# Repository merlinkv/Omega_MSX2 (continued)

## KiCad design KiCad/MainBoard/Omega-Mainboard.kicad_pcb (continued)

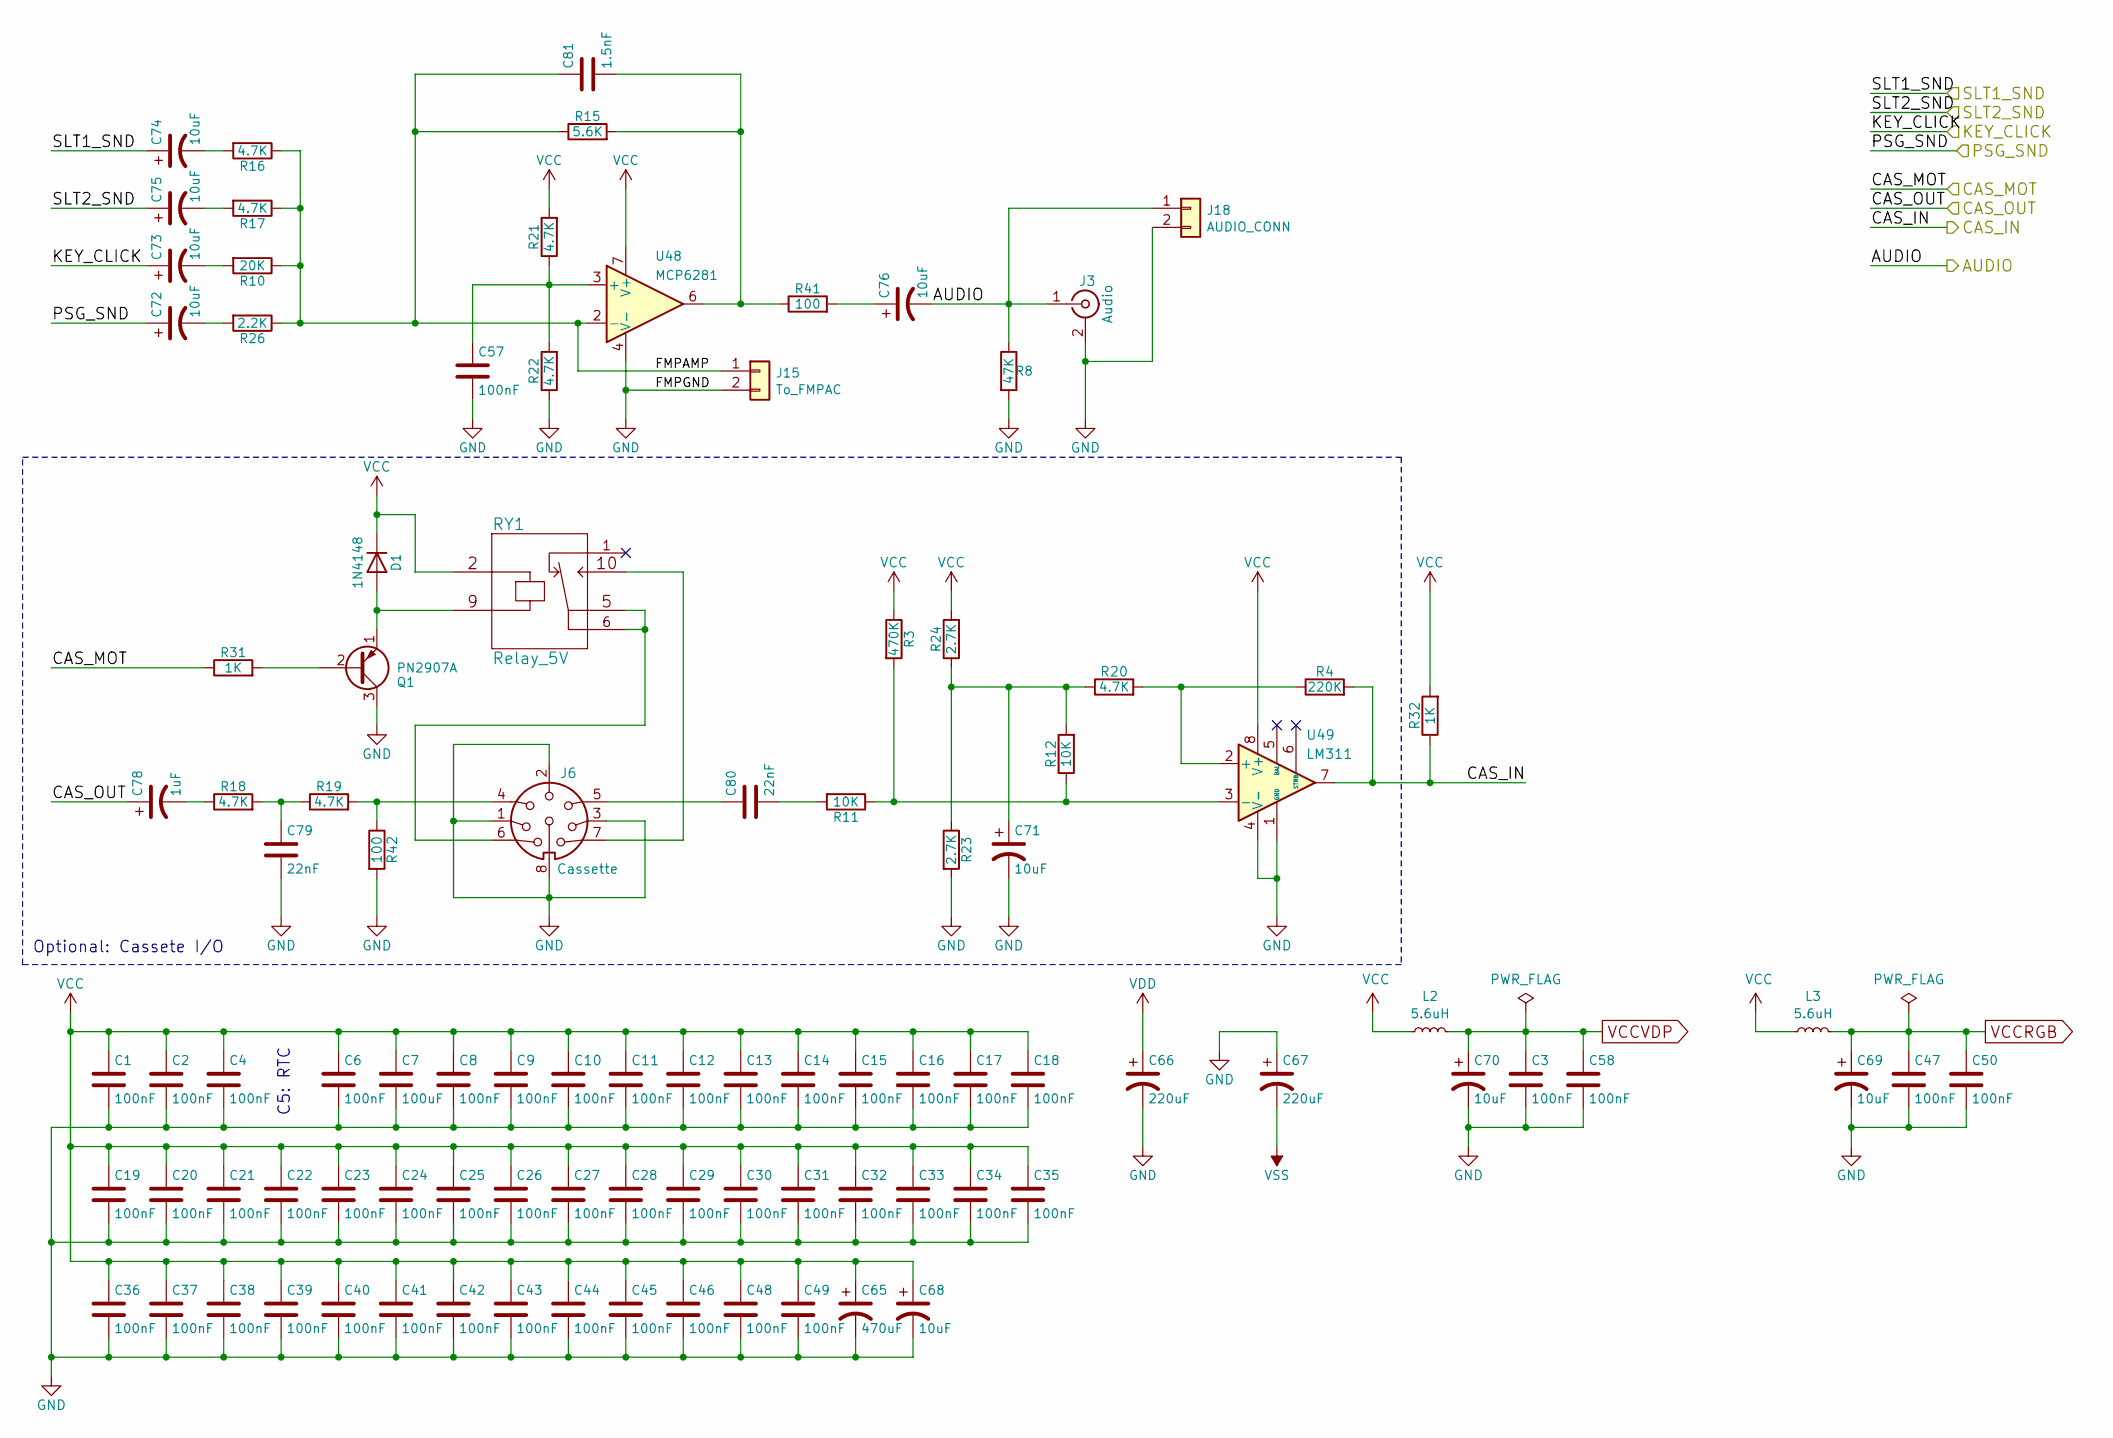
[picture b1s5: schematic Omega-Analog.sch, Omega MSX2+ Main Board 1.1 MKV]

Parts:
C1, C2, C3, C4, C6, C8, C9, C10, C11, C12, C13, C14, C15, C16, C17, C18, C19, C20, C21, C22, C23, C24, C25, C26, C27, C28, C29, C30, C31, C32, C33, C34, C35, C36, C37, C38, C39, C40, C41, C42, C43, C44, C45, C46, C47, C48, C49, C50, C57, C58: 100nF; C_1206_3216Metric_Pad1.42x1.75mm_HandSolder
C7: 100uF; C_1206_3216Metric_Pad1.42x1.75mm_HandSolder
C65: 470uF; CP_Radial_D10.0mm_P5.00mm
C66, C67: 220uF; CP_Radial_D10.0mm_P5.00mm
C68, C69, C70, C71, C72, C73, C74, C75, C76: 10uF; CP_Radial_D5.0mm_P2.50mm
C78: 1uF; CP_Radial_D5.0mm_P2.50mm
C79, C80: 22nF; C_1206_3216Metric_Pad1.42x1.75mm_HandSolder
C81: 1.5nF; C_1206_3216Metric_Pad1.42x1.75mm_HandSolder
D1: 1N4148; D_1206_3216Metric_Pad1.42x1.75mm_HandSolder
J3: Audio; Conn_RCA_Right
J6: Cassette; DIN8
J15: To_FMPAC; Molex_KK-254_AE-6410-02A_1x02_P2.54mm_Vertical
J18: AUDIO_CONN; Molex_KK-254_AE-6410-02A_1x02_P2.54mm_Vertical
L2, L3: 5.6uH; L_1206_3216Metric_Pad1.42x1.75mm_HandSolder
Q1: PN2907A; TO-92L_Inline_Wide
R3: 470K; R_1206_3216Metric_Pad1.42x1.75mm_HandSolder
R4: 220K; R_1206_3216Metric_Pad1.42x1.75mm_HandSolder
R8: 47K; R_1206_3216Metric_Pad1.42x1.75mm_HandSolder
R10: 20K; R_1206_3216Metric_Pad1.42x1.75mm_HandSolder
R11, R12: 10K; R_1206_3216Metric_Pad1.42x1.75mm_HandSolder
R15: 5.6K; R_1206_3216Metric_Pad1.42x1.75mm_HandSolder
R16, R17, R18, R19, R20, R21, R22: 4.7K; R_1206_3216Metric_Pad1.42x1.75mm_HandSolder
R23, R24: 2.7K; R_1206_3216Metric_Pad1.42x1.75mm_HandSolder
R26: 2.2K; R_1206_3216Metric_Pad1.42x1.75mm_HandSolder
R31, R32: 1K; R_1206_3216Metric_Pad1.42x1.75mm_HandSolder
R41, R42: 100; R_1206_3216Metric_Pad1.42x1.75mm_HandSolder
RY1: Relay_5V; Relay_SPDT
U48: MCP6281; DIP-8_W7.62mm_Socket
U49: LM311; DIP-8_W7.62mm_Socket

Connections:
/AUDIO: C76.2, J3.1 (In), J18.1, R8.1; also elsewhere on the board
/Analog/FMPAMP: C81.1, J15.1, R10.1, R15.1, R16.1, R17.1, R26.1, U48.2 (-)
/CAS_IN: R4.2, R32.1, U49.7; also elsewhere on the board
/CAS_MOT: R31.1; also elsewhere on the board
/CAS_OUT: C78.1; also elsewhere on the board
/KEY_CLICK: C73.1; also elsewhere on the board
/PSG_SND: C72.1; also elsewhere on the board
/SLT1_SND: C74.1; also elsewhere on the board
/SLT2_SND: C75.1; also elsewhere on the board
GND: C1.2, C2.2, C3.2, C4.2, C6.2, C7.2, C8.2, C9.2, C10.2, C11.2, C12.2, C13.2, C14.2, C15.2, C16.2, C17.2, C18.2, C19.2, C20.2, C21.2, C22.2, C23.2, C24.2, C25.2, C26.2, C27.2, C28.2, C29.2, C30.2, C31.2, C32.2, C33.2, C34.2, C35.2, C36.2, C37.2, C38.2, C39.2, C40.2, C41.2, C42.2, C43.2, C44.2, C45.2, C46.2, C47.2, C48.2, C49.2, C50.2, C57.2, C58.2, C65.2, C66.2, C67.1, C68.2, C69.2, C70.2, C71.2, C79.2, J3.2 (Ext), J6.1, J6.2, J6.3, J6.8, J15.2, J18.2, Q1.3 (C), R8.2, R22.1, R23.2, R42.2, U48.4 (V-), U49.1 (GND), U49.4 (V-); also elsewhere on the board
unnamed: C57.1, R21.1, R22.2, U48.3 (+)
unnamed: C71.1, R12.2, R20.1, R23.1, R24.1
unnamed: C72.2, R26.2
unnamed: C73.2, R10.2
unnamed: C74.2, R16.2
unnamed: C75.2, R17.2
unnamed: C76.1, R41.2
unnamed: C78.2, R18.1
unnamed: C79.1, R18.2, R19.1
unnamed: C80.1, J6.5
unnamed: C80.2, R11.2
unnamed: C81.2, R15.2, R41.1, U48.6
unnamed: D1.2 (A), Q1.1 (E), RY1.9
unnamed: J6.4, R19.2, R42.1
unnamed: J6.6, RY1.5, RY1.6
unnamed: J6.7, RY1.10
unnamed: Q1.2 (B), R31.2
unnamed: R3.2, R11.1, R12.1, U49.3 (-)
unnamed: R4.1, R20.2, U49.2 (+)
VCC: C1.1, C2.1, C4.1, C6.1, C7.1, C8.1, C9.1, C10.1, C11.1, C12.1, C13.1, C14.1, C15.1, C16.1, C17.1, C18.1, C19.1, C20.1, C21.1, C22.1, C23.1, C24.1, C25.1, C26.1, C27.1, C28.1, C29.1, C30.1, C31.1, C32.1, C33.1, C34.1, C35.1, C36.1, C37.1, C38.1, C39.1, C40.1, C41.1, C42.1, C43.1, C44.1, C45.1, C46.1, C48.1, C49.1, C65.1, C68.1, D1.1 (K), L2.1, L3.1, R3.1, R21.2, R24.2, R32.2, RY1.2, U48.7 (V+), U49.8 (V+); also elsewhere on the board
VCCRGB: C47.1, C50.1, C69.1, L3.2; also elsewhere on the board
VCCVDP: C3.1, C58.1, C70.1, L2.2; also elsewhere on the board
VDD: C66.1; also elsewhere on the board
VSS: C67.2; also elsewhere on the board

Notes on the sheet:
C5: RTC
Optional: Cassete I/O

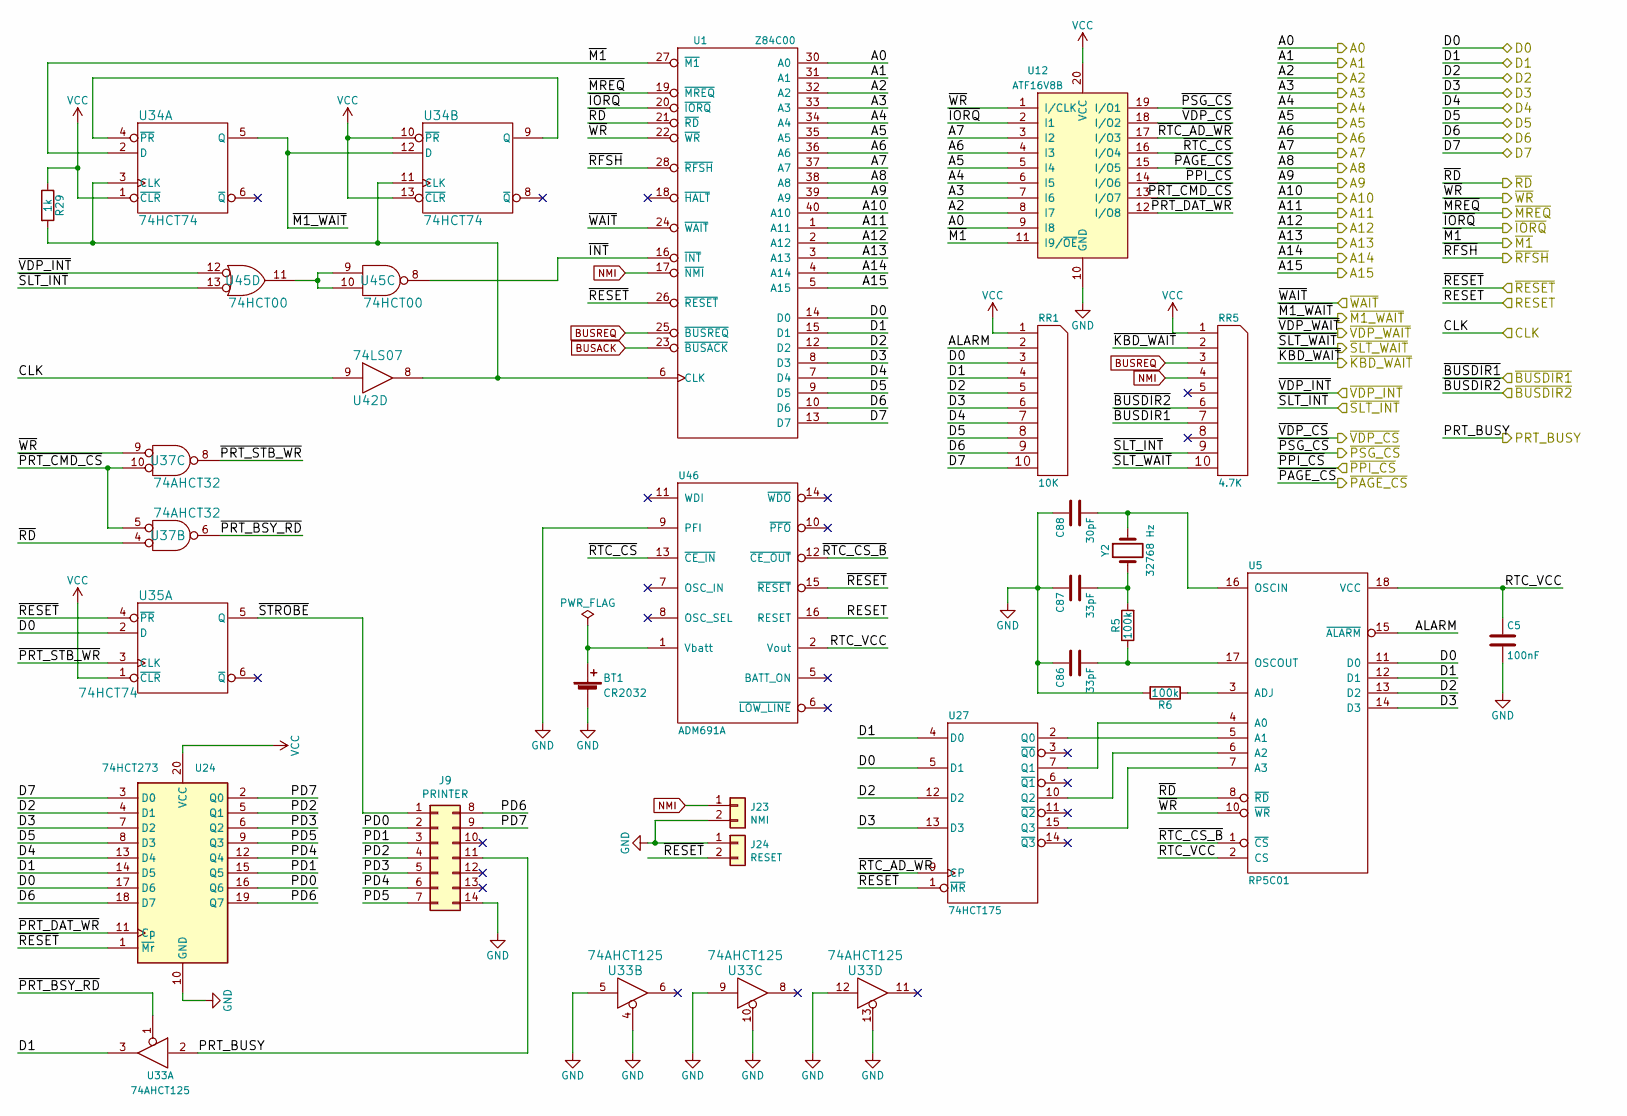
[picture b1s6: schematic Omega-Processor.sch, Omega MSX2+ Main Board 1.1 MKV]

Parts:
BT1: CR2032; Battery_Holder_CR2032_Universal
C5: 100nF; C_1206_3216Metric_Pad1.42x1.75mm_HandSolder
C86, C87: 33pF; C_1206_3216Metric_Pad1.42x1.75mm_HandSolder
C88: 30pF; C_1206_3216Metric_Pad1.42x1.75mm_HandSolder
J9: PRINTER; Conn_Micro_Ribbon_14F
J23: NMI; Molex_KK-254_AE-6410-02A_1x02_P2.54mm_Vertical
J24: RESET; Molex_KK-254_AE-6410-02A_1x02_P2.54mm_Vertical
R5, R6: 100k; R_1206_3216Metric_Pad1.42x1.75mm_HandSolder
R29: 1k; R_1206_3216Metric_Pad1.42x1.75mm_HandSolder
RR1: 10K; R_Array_SIP10
RR5: 4.7K; R_Array_SIP10
U1: Z84C00; DIP-40_W15.24mm_Socket
U5: RP5C01; DIP-18_W7.62mm_Socket
U12: ATF16V8B; DIP-20_W7.62mm_Socket
U24: 74HCT273; DIP-20_W7.62mm_Socket
U27: 74HCT175; DIP-16_W7.62mm_Socket
U33: 74AHCT125; DIP-14_W7.62mm_Socket
U34, U35: 74HCT74; DIP-14_W7.62mm_Socket
U37: 74AHCT32; IC_DIP14_300
U42: 74LS07; IC_DIP14_300
U45: 74HCT00; IC_DIP14_300
U46: ADM691A; DIP-16_W7.62mm_Socket
Y2: 32768 Hz; Crystal_C38-LF_D3.0mm_L8.0mm_Horizontal_1EP_style2

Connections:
/A0: U1.30 (A0), U12.9 (I8); also elsewhere on the board
/A1: U1.31 (A1); also elsewhere on the board
/A2: U1.32 (A2), U12.8 (I7); also elsewhere on the board
/A3: U1.33 (A3), U12.7 (I6); also elsewhere on the board
/A4: U1.34 (A4), U12.6 (I5); also elsewhere on the board
/A5: U1.35 (A5), U12.5 (I4); also elsewhere on the board
/A6: U1.36 (A6), U12.4 (I3); also elsewhere on the board
/A7: U1.37 (A7), U12.3 (I2); also elsewhere on the board
/A8: U1.38 (A8); also elsewhere on the board
/A9: U1.39 (A9); also elsewhere on the board
/A10: U1.40 (A10); also elsewhere on the board
/A11: U1.1 (A11); also elsewhere on the board
/A12: U1.2 (A12); also elsewhere on the board
/A13: U1.3 (A13); also elsewhere on the board
/A14: U1.4 (A14); also elsewhere on the board
/A15: U1.5 (A15); also elsewhere on the board
/CLK: U42.9; also elsewhere on the board
/D0: RR1.3, U1.14 (D0), U5.11 (D0), U24.17 (D6), U27.5 (D1), U35.2 (D); also elsewhere on the board
/D1: RR1.4, U1.15 (D1), U5.12 (D1), U24.14 (D5), U27.4 (D0), U33.3; also elsewhere on the board
/D2: RR1.5, U1.12 (D2), U5.13 (D2), U24.4 (D1), U27.12 (D2); also elsewhere on the board
/D3: RR1.6, U1.8 (D3), U5.14 (D3), U24.7 (D2), U27.13 (D3); also elsewhere on the board
/D4: RR1.7, U1.7 (D4), U24.13 (D4); also elsewhere on the board
/D5: RR1.8, U1.9 (D5), U24.8 (D3); also elsewhere on the board
/D6: RR1.9, U1.10 (D6), U24.18 (D7); also elsewhere on the board
/D7: RR1.10, U1.13 (D7), U24.3 (D0); also elsewhere on the board
/Memory/~PAGE_RD: U37.3; also elsewhere on the board
/Memory/~PAGE_WR: U37.11; also elsewhere on the board
/PRT_BUSY: J9.11, U33.2; also elsewhere on the board
/Processor/ALARM: RR1.2, U5.15 (~ALARM)
/Processor/PD0: J9.2, U24.16 (Q6)
/Processor/PD1: J9.3, U24.15 (Q5)
/Processor/PD2: J9.4, U24.5 (Q1)
/Processor/PD3: J9.5, U24.6 (Q2)
/Processor/PD4: J9.6, U24.12 (Q4)
/Processor/PD5: J9.7, U24.9 (Q3)
/Processor/PD6: J9.8, U24.19 (Q7)
/Processor/PD7: J9.9, U24.2 (Q0)
/Processor/RTC_VCC: C5.1, U5.2 (CS), U5.18 (VCC), U46.2 (Vout)
/Processor/~INT: U1.16 (~INT), U45.8
/Processor/~PRT_BSY_RD: U33.1, U37.6
/Processor/~PRT_CMD_CS: U12.13 (I/O7), U37.5, U37.10
/Processor/~PRT_DAT_WR: U12.12 (I/O8), U24.11 (Cp)
/Processor/~PRT_STB_WR: U35.3 (CLK), U37.8
/Processor/~RTC_AD_WR: U12.17 (I/O3), U27.9 (CP)
/Processor/~RTC_CS: U12.16 (I/O4), U46.13 (~CE_IN)
/Processor/~RTC_CS_B: U5.1 (~CS), U46.12 (~CE_OUT)
/Processor/~STROBE: J9.1, U35.5 (Q)
/RESET: U46.16 (RESET); also elsewhere on the board
/~BUSDIR1: RR5.7; also elsewhere on the board
/~BUSDIR2: RR5.6; also elsewhere on the board
/~IORQ: U1.20 (~IORQ), U12.2 (I1); also elsewhere on the board
/~KBD_WAIT: RR5.2; also elsewhere on the board
/~M1: U1.27 (~M1), U12.11 (I9/~OE), U34.2 (D); also elsewhere on the board
/~M1_WAIT: U34.5 (Q), U34.12 (D); also elsewhere on the board
/~MREQ: U1.19 (~MREQ); also elsewhere on the board
/~PAGE_CS: U12.15 (I/O5), U37.2, U37.12
/~PPI_CS: U12.14 (I/O6), U45.4; also elsewhere on the board
/~PSG_CS: U12.19 (I/O1); also elsewhere on the board
/~RD: U1.21 (~RD), U5.8 (~RD), U37.1, U37.4; also elsewhere on the board
/~RESET: J24.2, U1.26 (~RESET), U24.1 (~Mr), U27.1 (~MR), U35.4 (~PR), U45.2, U46.15 (~RESET); also elsewhere on the board
/~RFSH: U1.28 (~RFSH); also elsewhere on the board
/~SLT_INT: RR5.9, U45.13; also elsewhere on the board
/~SLT_WAIT: RR5.10; also elsewhere on the board
/~VDP_CS: U12.18 (I/O2); also elsewhere on the board
/~VDP_INT: U45.12; also elsewhere on the board
/~WAIT: U1.24 (~WAIT); also elsewhere on the board
/~WR: U1.22 (~WR), U5.10 (~WR), U12.1 (I/CLK), U37.9, U37.13; also elsewhere on the board
BUSACK: U1.23 (~BUSACK); also elsewhere on the board
BUSREQ: RR5.3, U1.25 (~BUSREQ); also elsewhere on the board
GND: BT1.2 (-), C5.2, C86.1, C87.1, C88.1, J9.14, J23.2, J24.1, R6.2, U1.29 (GND), U5.9 (GND), U12.10 (GND), U24.10 (GND), U27.8 (GND), U33.4, U33.5, U33.7 (GND), U33.9, U33.10, U33.12, U33.13, U34.7 (GND), U35.7 (GND), U37.7 (GND), U42.7 (GND), U45.7 (GND), U46.4 (GND), U46.9 (PFI); also elsewhere on the board
NMI: J23.1, RR5.4, U1.17 (~NMI); also elsewhere on the board
unnamed: BT1.1 (+), U46.1 (Vbatt)
unnamed: C86.2, R5.1, U5.17 (OSCOUT)
unnamed: C87.2, R5.2, Y2.2
unnamed: C88.2, U5.16 (OSCIN), Y2.1
unnamed: R6.1, U5.3 (ADJ)
unnamed: R29.2, U1.6 (CLK), U34.3 (CLK), U34.11 (CLK), U42.8
unnamed: U5.5 (A1), U27.2 (Q0)
unnamed: U5.4 (A0), U27.7 (Q1)
unnamed: U5.6 (A2), U27.10 (Q2)
unnamed: U5.7 (A3), U27.15 (Q3)
unnamed 379: U45.3, U45.5; also elsewhere on the board
unnamed: U34.4 (~PR), U34.9 (Q)
unnamed: U45.1, U45.6
unnamed: U45.9, U45.10, U45.11
VCC: R29.1, RR1.1 (COM), RR5.1 (COM), U1.11 (VCC), U12.20 (VCC), U24.20 (VCC), U27.16 (VCC), U33.14 (VCC), U34.1 (~CLR), U34.10 (~PR), U34.13 (~CLR), U34.14 (VCC), U35.1 (~CLR), U35.14 (VCC), U37.14 (VCC), U42.14 (VCC), U45.14 (VCC), U46.3 (VCC); also elsewhere on the board

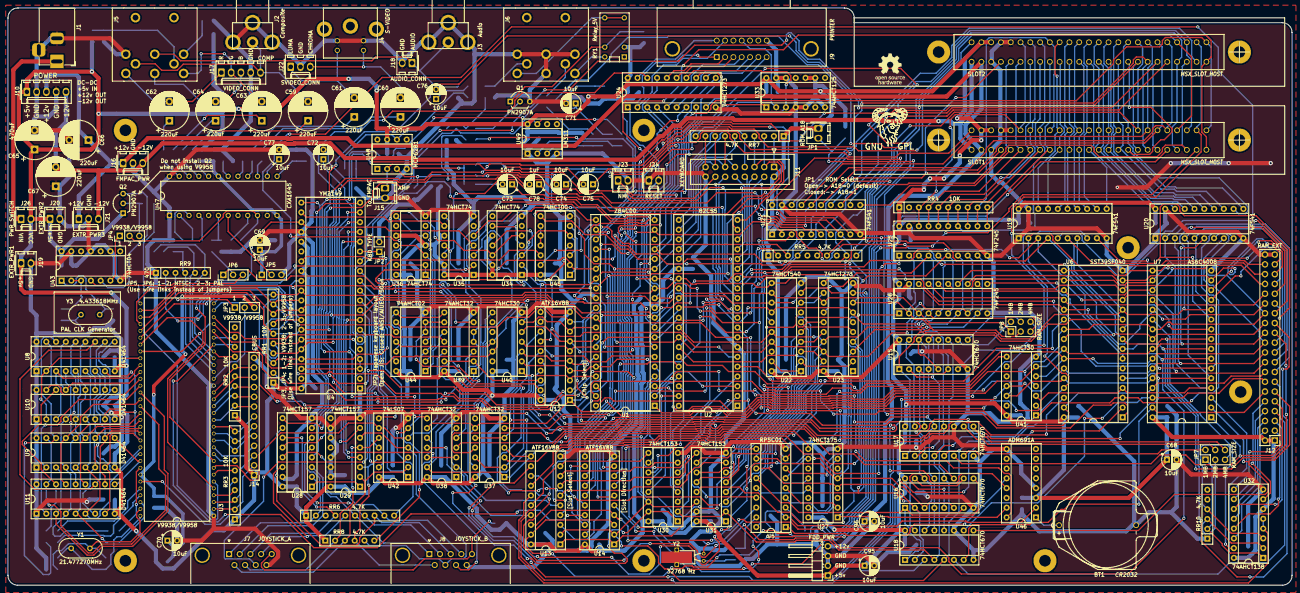
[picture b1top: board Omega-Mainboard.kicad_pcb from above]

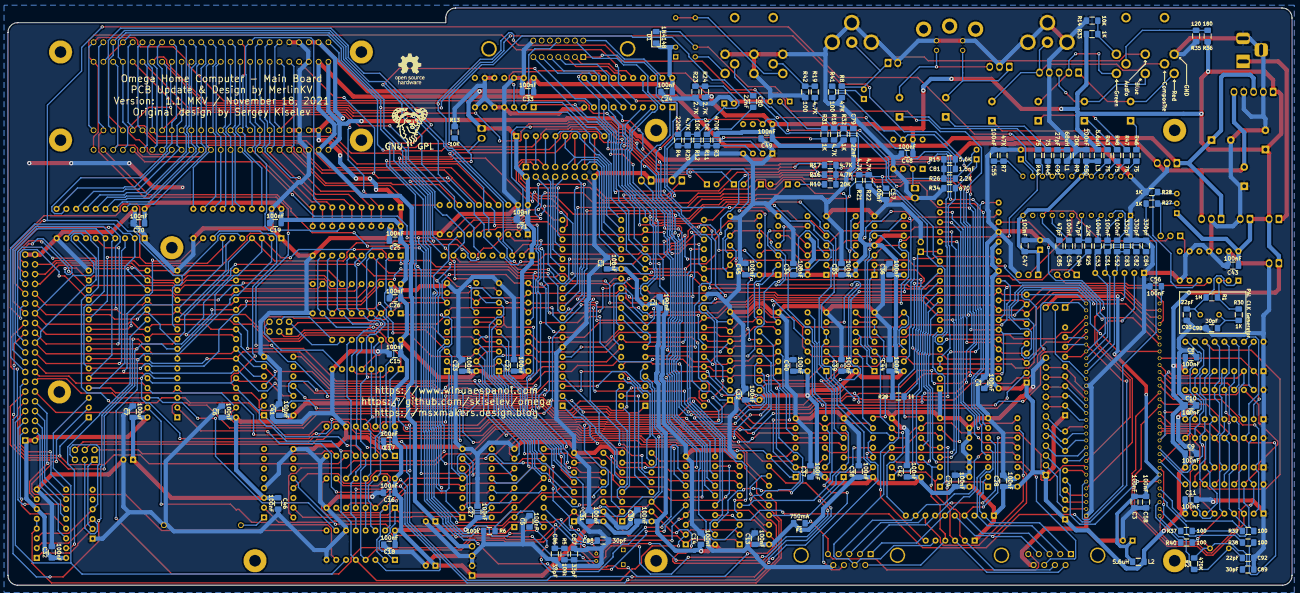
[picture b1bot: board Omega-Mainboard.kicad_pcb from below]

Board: 2 copper layers, 333.4 x 149.9 mm, 261 parts (127 on the bottom side), 365 nets.

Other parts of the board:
J11: KEYBOARD; IDC-Header_2x08_P2.54mm_Vertical
J12: RAM_EXT; PinHeader_2x20_P2.54mm_Vertical
JP1: ROM_A18; Molex_KK-254_AE-6410-02A_1x02_P2.54mm_Vertical
JP7, JP8: RAM_SIZE; PinHeader_2x03_P2.54mm_Vertical
R13: 10K; R_1206_3216Metric_Pad1.42x1.75mm_HandSolder
RR7: 4.7K; R_Array_SIP10
RR10: 4.7K; R_Array_SIP6
U2: 82C55; DIP-40_W15.24mm_Socket
U6: SST39SF040; DIP-32_W15.24mm_Socket
U7: AS6C4008; DIP-32_W15.24mm_Socket
U13: ATF16V8B; DIP-20_W7.62mm_Socket
U15, U16, U17, U18: 74HCT670; DIP-16_W7.62mm_Socket
U22: 74HCT540; DIP-20_W7.62mm_Socket
U23: 74HCT273; DIP-20_W7.62mm_Socket
U26: 74F245; DIP-20_W7.62mm_Socket
U30, U31: 74HCT153; DIP-16_W7.62mm_Socket
U32: 74AHCT138; DIP-16_W7.62mm_Socket
U38: 74AHCT32; DIP-14_W7.62mm_Socket
U40, U41: 74HCT30; DIP-14_W7.62mm_Socket

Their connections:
/A0: J12.31, U2.9, U6.12, U7.12, U15.5, U15.14, U16.5, U16.14, U17.14, U18.14, U40.12; also elsewhere on the board
/A1: J12.29, U2.8, U6.11, U7.11, U15.4, U15.13, U16.4, U16.13, U17.13, U18.13, U40.11; also elsewhere on the board
/A2: J12.27, U6.10, U7.10, U40.6; also elsewhere on the board
/A3: J12.25, U6.9, U7.9, U40.5; also elsewhere on the board
/A4: J12.23, U6.8, U7.8, U40.4; also elsewhere on the board
/A5: J12.21, U6.7, U7.7, U40.3; also elsewhere on the board
/A6: J12.19, U6.6, U7.6, U40.2; also elsewhere on the board
/A7: J12.17, U6.5, U7.5, U40.1; also elsewhere on the board
/A8: J12.20, U6.27, U7.27, U41.11; also elsewhere on the board
/A9: J12.22, U6.26, U7.26, U41.5; also elsewhere on the board
/A10: J12.28, U6.23, U7.23, U41.4; also elsewhere on the board
/A11: J12.24, U6.25, U7.25, U41.6; also elsewhere on the board
/A12: J12.15, U6.4, U7.4, U41.3; also elsewhere on the board
/A13: J12.18, U6.28, U7.28, U41.12; also elsewhere on the board
/A14: U6.29, U13.2, U17.5, U18.5, U30.14, U31.14, U41.2; also elsewhere on the board
/A15: U6.3, U13.1, U17.4, U18.4, U30.2, U31.2, U41.1; also elsewhere on the board
/CAS_MOT: U2.13; also elsewhere on the board
/CAS_OUT: U2.12; also elsewhere on the board
/D0: U2.34, U16.3, U16.6, U18.3, U22.18, U23.3, U26.9; also elsewhere on the board
/D1: U2.33, U16.2, U16.7, U18.2, U22.17, U23.18, U26.8; also elsewhere on the board
/D2: U2.32, U16.1, U16.9, U18.1, U22.16, U23.17, U26.7; also elsewhere on the board
/D3: U2.31, U16.10, U16.15, U18.15, U22.15, U23.4, U26.6; also elsewhere on the board
/D4: U2.30, U15.3, U15.6, U17.3, U22.14, U23.7, U26.5; also elsewhere on the board
/D5: JP8.5, U2.29, U15.2, U17.2, U22.13, U23.14, U26.4; also elsewhere on the board
/D6: JP8.1, U2.28, U15.15, U17.15, U22.12, U23.13, U26.3; also elsewhere on the board
/D7: JP8.3, U2.27, U15.1, U17.1, U22.11, U23.8, U26.2; also elsewhere on the board
/KANA_LED: J11.14; also elsewhere on the board
/KEY_CLICK: U2.10; also elsewhere on the board
/Memory/MD0: J12.33, U6.13, U7.13, U26.11
/Memory/MD1: J12.35, U6.14, U7.14, U26.12
/Memory/MD2: J12.37, U6.15, U7.15, U26.13
/Memory/MD3: J12.38, U6.17, U7.17, U26.14
/Memory/MD4: J12.36, U6.18, U7.18, U26.15
/Memory/MD5: J12.34, U6.19, U7.19, U26.16
/Memory/MD6: J12.32, U6.20, U7.20, U26.17
/Memory/MD7: J12.30, U6.21, U7.21, U26.18
/Memory/RAM_A14: J12.13, U7.3, U18.6
/Memory/RAM_A15: J12.12, U7.31, U18.7
/Memory/RAM_A16: J12.11, U7.2, U18.9
/Memory/RAM_A17: J12.14, U7.30, U18.10
/Memory/RAM_A18: J12.9, U7.1, U17.6
/Memory/RAM_A19: JP7.2, U17.7
/Memory/RAM_A20: JP7.4, U17.10
/Memory/RAM_A21: JP7.6, U17.9
/Memory/ROM_A18: JP1.2, R13.1, U6.1
/Memory/~PAGE_RD: U15.11, U16.11; also elsewhere on the board
/Memory/~PAGE_WR: U15.12, U16.12, U17.12, U18.12; also elsewhere on the board
/Memory/~RAM0_CS: U7.22, U32.15
/Memory/~RAM1_CS: J12.4, U32.14
/Memory/~RAM2_CS: J12.3, U32.13
/Memory/~RAM3_CS: J12.6, U32.12
/Memory/~RAM4_CS: J12.5, U32.11
/Memory/~RAM5_CS: J12.8, U32.10
/Memory/~RAM6_CS: J12.7, U32.9
/Memory/~RAM7_CS: J12.10, U32.7
/PPI/CAPS_LED: J11.12, U2.11
/PPI/COLUMN0: J11.1, RR7.2, U2.18
/PPI/COLUMN1: J11.3, RR7.3, U2.19
/PPI/COLUMN2: J11.5, RR7.4, U2.20
/PPI/COLUMN3: J11.7, RR7.5, U2.21
/PPI/COLUMN4: J11.9, RR7.6, U2.22
/PPI/COLUMN5: J11.11, RR7.7, U2.23
/PPI/COLUMN6: J11.13, RR7.8, U2.24
/PPI/COLUMN7: J11.15, RR7.9, U2.25
/PPI/ROW_A: J11.4, U2.14
/PPI/ROW_B: J11.6, U2.15
/PPI/ROW_C: J11.8, U2.16
/PPI/ROW_D: J11.10, U2.17
/PPI/SB_SLT_A: U13.6, U31.7
/PPI/SB_SLT_B: U13.7, U31.9
/PPI/SLT_A: U13.8, U30.7
/PPI/SLT_B: U13.9, U30.9
/PPI/~FFFF: U13.5, U38.2, U38.6
/PPI/~SLTSL3: U13.17, U38.1
/PPI/~SUB_RD: U22.1, U22.19, U38.11
/PPI/~SUB_REG_CS: U38.3, U38.10, U38.12
/PPI/~SUB_WR: U23.11, U38.8
/PRT_BUSY: RR7.10; also elsewhere on the board
/RESET: U2.35; also elsewhere on the board
/ROM_A16: U6.2, U13.13
/ROM_A17: U6.30, U13.12
/~MEM_RD: U13.16, U26.1
/~MREQ: U13.3; also elsewhere on the board
/~PPI_CS: U2.6; also elsewhere on the board
/~RAM_SL: U13.15, U32.4, U32.5
/~RD: J12.26, U2.5, U6.24, U7.24, U13.11, U38.13; also elsewhere on the board
/~RESET: U23.1; also elsewhere on the board
/~RFSH: U13.4; also elsewhere on the board
/~ROM_CS: U6.22, U13.14
/~SLTSL1: U13.19; also elsewhere on the board
/~SLTSL2: U13.18; also elsewhere on the board
/~WR: J12.16, U2.36, U6.31, U7.29, U38.9; also elsewhere on the board
GND: J11.16, J12.39, J12.40, R13.2, RR10.1, U2.7, U6.16, U7.16, U13.10, U15.8, U16.8, U17.8, U17.11, U18.8, U18.11, U22.10, U23.10, U26.10, U26.19, U30.8, U31.1, U31.8, U31.15, U32.8, U38.7, U40.7, U41.7; also elsewhere on the board
unnamed: JP7.1, RR10.2, U32.1
unnamed: JP7.3, RR10.3, U32.2
unnamed: JP7.5, RR10.4, U32.3
unnamed: JP8.2, U15.10
unnamed: JP8.4, U15.9
unnamed: JP8.6, U15.7
unnamed: U2.1, U30.11
unnamed: U2.2, U30.5
unnamed: U2.3, U30.10
unnamed: U2.4, U30.6
unnamed: U2.37, U30.13
unnamed: U2.38, U30.3
unnamed: U2.39, U30.12
unnamed: U2.40, U30.4
unnamed: U22.2, U23.2, U31.6
unnamed: U22.3, U23.19, U31.10
unnamed: U22.4, U23.16, U31.5
unnamed: U22.5, U23.5, U31.11
unnamed: U22.6, U23.6, U31.4
unnamed: U22.7, U23.15, U31.12
unnamed: U22.8, U23.12, U31.3
unnamed: U22.9, U23.9, U31.13
unnamed 379: U30.1, U30.15; also elsewhere on the board
unnamed: U38.4, U41.8
unnamed: U38.5, U40.8
VCC: J11.2, J12.1, J12.2, JP1.1, RR7.1, U2.26, U6.32, U7.32, U13.20, U15.16, U16.16, U17.16, U18.16, U22.20, U23.20, U26.20, U30.16, U31.16, U32.6, U32.16, U38.14, U40.14, U41.14; also elsewhere on the board

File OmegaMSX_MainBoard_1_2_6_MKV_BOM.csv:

"Id";"Designator";"Footprint";"Quantity";"Designation";"Supplier and ref";
1;"HOLE1,HOLE2,HOLE3,HOLE4,HOLE5,HOLE6,HOLE7,HOLE8,HOLE9,HOLE10,HOLE11";"MountingHole_3mm_Pad";11;"HOLE";;;
2;"C59,C60,C63,C64,C61,C62";"CP_Radial_D10.0mm_P5.00mm";6;"220uF";;;
3;"C65,C66,C67";"CP_Radial_D6.3mm_P2.50mm";3;"100uF";;;
4;"C72,C75,C76,C74,C77,C71,C73,C68,C69,C70";"CP_Radial_D5.0mm_P2.50mm";10;"10uF";;;
5;"J1";"BarrelJack_Horizontal";1;"5V";;;
6;"J7";"DSUB-9_Male_Horizontal_P2.77x2.84mm_EdgePinOffset4.94mm_Housed_MountingHolesOffset7.48mm";1;"JOYSTICK_A";;;
7;"J8";"DSUB-9_Male_Horizontal_P2.77x2.84mm_EdgePinOffset4.94mm_Housed_MountingHolesOffset7.48mm";1;"JOYSTICK_B";;;
8;"JP1";"Molex_KK-254_AE-6410-02A_1x02_P2.54mm_Vertical";1;"SEL_ROM1";;;
9;"JP2";"PinHeader_1x02_P2.54mm_Vertical";1;"KBD_TYPE";;;
10;"JP3,JP4";"PinHeader_1x03_P2.54mm_Vertical";2;"V9938/V9958";;;
11;"JP5,JP6";"PinHeader_1x03_P2.54mm_Vertical";2;"NTSC/PAL";;;
12;"RR1,RR2,RR3,RR4";"R_Array_SIP10";4;"10K";;;
13;"RR6,RR5,RR7";"R_Array_SIP10";3;"4.7K";;;
14;"RR8,RR10";"R_Array_SIP6";2;"4.7K";;;
15;"RR9";"R_Array_SIP6";1;"470";;;
16;"U2";"DIP-40_W15.24mm_Socket";1;"82C55";;;
17;"U3";"IC_SDIP64_600";1;"V9938/V9958";;;
18;"U4";"DIP-40_W15.24mm_Socket";1;"YM2149";;;
19;"U5";"DIP-18_W7.62mm_Socket";1;"RP5C01";;;
20;"U6,U50";"SST39SF040_PLCC32";2;"SST39SF040";;;
21;"U7";"DIP-32_W15.24mm_Socket";1;"AS6C4008";;;
22;"U8,U9,U10,U11";"DIP-18_W7.62mm_Socket";4;"D41464";;;
23;"U12,U14,U13";"DIP-20_W7.62mm_Socket";3;"ATF16V8B";;;
24;"U15,U17,U18,U16";"DIP-16_W7.62mm_Socket";4;"74HCT670";;;
25;"U20,U21,U19";"DIP-20_W7.62mm_Socket";3;"74F541";;;
26;"U23,U24";"DIP-20_W7.62mm_Socket";2;"74HCT273";;;
27;"U25,U26";"DIP-20_W7.62mm_Socket";2;"74F245";;;
28;"U27";"DIP-16_W7.62mm_Socket";1;"74HCT175";;;
29;"U28,U29";"DIP-16_W7.62mm_Socket";2;"74HCT157";;;
30;"U31,U30";"DIP-16_W7.62mm_Socket";2;"74HCT153";;;
31;"U33";"DIP-14_W7.62mm_Socket";1;"74AHCT125";;;
32;"U34,U35,U36";"DIP-14_W7.62mm_Socket";3;"74HCT74";;;
33;"U38,U39,U37";"DIP-14_W7.62mm_Socket";3;"74AHCT32";;;
34;"U42";"DIP-14_W7.62mm_Socket";1;"74LS07";;;
35;"U44";"DIP-14_W7.62mm_Socket";1;"74AHCT02";;;
36;"U45";"DIP-14_W7.62mm_Socket";1;"74HCT00";;;
37;"U47";"IC_DIP24_400";1;"CXA1645";;;
38;"Y3";"Crystal_HC49-U_Vertical";1;"4.433618MHz";;;
39;"J3";"Conn_RCA_Right";1;"Audio";;;
40;"U22";"DIP-20_W7.62mm_Socket";1;"74HCT540";;;
41;"U40,U41";"DIP-14_W7.62mm_Socket";2;"74HCT30";;;
42;"J11";"IDC-Header_2x08_P2.54mm_Vertical";1;"KEYBOARD";;;
43;"Q2,Q1";"TO-92L_Inline_Wide";2;"PN2907A";;;
44;"J12";"PinHeader_2x20_P2.54mm_Vertical";1;"RAM_EXT";;;
45;"BT1";"Battery_Holder_CR2032_Universal";1;"CR2032";;;
46;"U46";"DIP-16_W7.62mm_Socket";1;"ADM691A";;;
47;"J9";"Conn_Micro_Ribbon_14F";1;"PRINTER";;;
48;"J4";"Conn_Mini_DIN_4pin";1;"S-VIDEO";;;
49;"U48";"DIP-8_W7.62mm_Socket";1;"MCP6281";;;
50;"U43";"DIP-14_W7.62mm_Socket";1;"74HCT04";;;
51;"J6";"DIN8";1;"Cassette";;;
52;"RY1";"Relay_SPDT";1;"Relay_5V";;;
53;"C78";"CP_Radial_D5.0mm_P2.50mm";1;"1uF";;;
54;"U49";"DIP-8_W7.62mm_Socket";1;"LM311";;;
55;"J5";"DIN8";1;"RGB";;;
56;"J2";"Conn_RCA_Right";1;"Composite";;;
57;"Y1";"Crystal_HC49-U_Vertical";1;"21.477270MHz";;;
58;"Y2";"Crystal_C38-LF_D3.0mm_L8.0mm_Horizontal_1EP_style2";1;"32768 Hz";;;
59;"J14";"PinHeader_1x13_P2.54mm_Vertical";1;"CBUS";;;
60;"JP7,JP8";"PinHeader_2x03_P2.54mm_Vertical";2;"RAM_SIZE";;;
61;"U32";"DIP-16_W7.62mm_Socket";1;"74AHCT138";;;
62;"J15";"Molex_KK-254_AE-6410-02A_1x02_P2.54mm_Vertical";1;"To_FMPAC";;;
63;"J16";"Molex_KK-254_AE-6410-03A_1x03_P2.54mm_Vertical";1;"FMPAC_PWR";;;
64;"J25";"Molex_KK-254_AE-6410-04A_1x04_P2.54mm_Vertical";1;"FDD_PWR";;;
65;"J21";"Molex_KK-254_AE-6410-03A_1x03_P2.54mm_Vertical";1;"EXTR_PWR3";;;
66;"SLOT1,SLOT2";"Conn_Edge_50P";2;"MSX_SLOT_HOST";;;
67;"U1";"DIP-40_W15.24mm_Socket";1;"Z84C00";;;
68;"J22";"Molex_KK-254_AE-6410-03A_1x03_P2.54mm_Vertical";1;"SVIDEO_CONN";;;
69;"J19";"Molex_KK-254_AE-6410-02A_1x02_P2.54mm_Vertical";1;"EXTR_PWR1";;;
70;"J20";"Molex_KK-254_AE-6410-02A_1x02_P2.54mm_Vertical";1;"EXTR_PWR2";;;
71;"J17";"Molex_KK-254_AE-6410-05A_1x05_P2.54mm_Vertical";1;"VIDEO_CONN";;;
72;"J18";"Molex_KK-254_AE-6410-02A_1x02_P2.54mm_Vertical";1;"AUDIO_CONN";;;
73;"J23";"Molex_KK-254_AE-6410-02A_1x02_P2.54mm_Vertical";1;"NMI";;;
74;"J24";"Molex_KK-254_AE-6410-02A_1x02_P2.54mm_Vertical";1;"RESET";;;
75;"J10";"Molex_KK-254_AE-6410-05A_1x05_P2.54mm_Vertical";1;"DC Converter";;;
76;"J26";"Molex_KK-254_AE-6410-02A_1x02_P2.54mm_Vertical_Omega";1;"PWR_SWITCH";;;
77;"JP9";"Molex_KK-254_AE-6410-02A_1x02_P2.54mm_Vertical";1;"SEL_ROM2";;;
78;"SW2";"Molex_KK-254_AE-6410-03A_1x03_P2.54mm_Vertical";1;"SEL_ROM";;;
79;"J27";"Molex_KK-254_AE-6410-02A_1x02_P2.54mm_Vertical";1;"EXTR_PWR4";;;
80;"C1,C2,C4,C5,C6,C7,C8,C9,C10,C11,C12,C13,C14,C15,C17,C18,C20,C21,C22,C24,C25,C26,C27,C28,C29,C30,C31,C32,C33,C34,C35,C36,C37,C38,C39,C40,C41,C42,C43,C44,C45,C46,C47,C52,C56,C23,C54,C51,C53,C19,C16,C48,C57,C49,C55,C58,C3,C50,C100";"C_1206_3216Metric_Pad1.33x1.80mm_HandSolder";59;"100nF";;;
81;"C80,C79";"C_1206_3216Metric_Pad1.33x1.80mm_HandSolder";2;"22nF";;;
82;"C82,C83,C84";"C_1206_3216Metric_Pad1.33x1.80mm_HandSolder";3;"330pF";;;
83;"C85";"C_1206_3216Metric_Pad1.33x1.80mm_HandSolder";1;"47pF";;;
84;"C86,C87";"C_1206_3216Metric_Pad1.33x1.80mm_HandSolder";2;"33pF";;;
85;"C92,C93";"C_1206_3216Metric_Pad1.33x1.80mm_HandSolder";2;"22pF";;;
86;"D1";"D_1206_3216Metric_Pad1.42x1.75mm_HandSolder";1;"1N4148";;;
87;"R1";"R_1206_3216Metric_Pad1.30x1.75mm_HandSolder";1;"1M";;;
88;"R2,R3";"R_1206_3216Metric_Pad1.30x1.75mm_HandSolder";2;"470K";;;
89;"R5,R6";"R_1206_3216Metric_Pad1.30x1.75mm_HandSolder";2;"100K";;;
90;"R7,R8";"R_1206_3216Metric_Pad1.30x1.75mm_HandSolder";2;"47K";;;
91;"R17,R21,R22,R16,R19,R18,R20";"R_1206_3216Metric_Pad1.30x1.75mm_HandSolder";7;"4.7K";;;
92;"R25,R26";"R_1206_3216Metric_Pad1.30x1.75mm_HandSolder";2;"2.2K";;;
93;"R30,R29,R27,R28,R31,R32,R33";"R_1206_3216Metric_Pad1.30x1.75mm_HandSolder";7;"1K";;;
94;"R37,R39,R40,R41,R38,R42";"R_1206_3216Metric_Pad1.30x1.75mm_HandSolder";6;"100";;;
95;"R47,R48,R45,R44,R43,R46";"R_1206_3216Metric_Pad1.30x1.75mm_HandSolder";6;"75";;;
96;"R9,R10";"R_1206_3216Metric_Pad1.30x1.75mm_HandSolder";2;"20K";;;
97;"C94";"C_1206_3216Metric_Pad1.33x1.80mm_HandSolder";1;"4.7pF";;;
98;"C81";"C_1206_3216Metric_Pad1.33x1.80mm_HandSolder";1;"1.5nF";;;
99;"R13,R12,R11,R14,R49,R50,R51";"R_1206_3216Metric_Pad1.30x1.75mm_HandSolder";7;"10K";;;
100;"R15";"R_1206_3216Metric_Pad1.30x1.75mm_HandSolder";1;"5.6K";;;
101;"L1";"L_1206_3216Metric_Pad1.42x1.75mm_HandSolder";1;"68uH";;;
102;"C91";"C_1206_3216Metric_Pad1.33x1.80mm_HandSolder";1;"27pF";;;
103;"R23,R24";"R_1206_3216Metric_Pad1.30x1.75mm_HandSolder";2;"2.7K";;;
104;"R4";"R_1206_3216Metric_Pad1.30x1.75mm_HandSolder";1;"220K";;;
105;"R35";"R_1206_3216Metric_Pad1.30x1.75mm_HandSolder";1;"180";;;
106;"R36";"R_1206_3216Metric_Pad1.30x1.75mm_HandSolder";1;"120";;;
107;"R34";"R_1206_3216Metric_Pad1.30x1.75mm_HandSolder";1;"470";;;
108;"L2,L3";"L_1206_3216Metric_Pad1.42x1.75mm_HandSolder";2;"5.6uH";;;
109;"F1";"Fuse_1206_3216Metric_Pad1.42x1.75mm_HandSolder";1;"750mA";;;
110;"C89,C90,C88";"C_1206_3216Metric_Pad1.33x1.80mm_HandSolder";3;"30pF";;;

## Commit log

2021-11-20 Create aaa
2021-12-20 Create Mainboard_1_1_MKV\aaa
2024-04-14 Create zzz
